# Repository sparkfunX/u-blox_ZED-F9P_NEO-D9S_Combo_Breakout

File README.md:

# SparkX u-blox ZED-F9P NEO-D9S Combo Breakout

<p align="center">

</p>

*[SparkX u-blox ZED-F9P NEO-D9S Combo Breakout (SPX-20167)](https://www.sparkfun.com/products/20167)*

The [SparkX u-blox ZED-F9P NEO-D9S Combo Breakout (SPX-20167)](https://www.sparkfun.com/products/20167) combines the u-blox ZED-F9P multi-band high precision GNSS module
with the NEO-D9S L-band GNSS correction data receiver. With a clear view of the sky, especially a clear view to the South, this combo breakout will deliver centimeter-level
accuracy positioning without needing separate RTK or NTRIP corrections.

The Combo Breakout is designed to work with u-blox's PointPerfect L-band satellite GNSS augmentation service, which provides homogeneous coverage in contiguous USA and Europe.

### Important Note:

u-blox provides products and services to "B2B Customers". Only business customers are eligible to register for a Thingstream (PointPerfect) account. You may be required to demonstrate that the use of the combo breakout is in relation to your trade, business, craft or profession. u-blox products and services are not intended for individual consumer use.

## Repository Contents

* **[/docs](/docs/)** - Online documentation files
    * [board_files](/docs/board_files/) - Files for the product design
        * [Eagle design files](/docs/board_files/ZED-F9P_NEO-D9S_Combo_x02.zip) (.zip)
        * [Schematic](/docs/board_files/Schematic.pdf) (.pdf)
        * [Dimensions](/docs/board_files/Dimensions.png) (.png)
    * [img/hookup_guide/](/docs/img/hookup_guide/) - Images for hookup guide documentation
* **[/Hardware](/Hardware/)** - Eagle design files (.brd, .sch)

## Documentation

* **[Hookup Guide (mkdocs)](https://sparkfunx.github.io/u-blox_ZED-F9P_NEO-D9S_Combo_Breakout)** - Hookup guide for the SparkX u-blox ZED-F9P NEO-D9S Combo Breakout hosted by GitHub pages.

## Product Versions

* [SPX-20167](https://www.sparkfun.com/products/20167) - Initial SparkX Release

## License Information

This product is _**open source**_! 

Please review the LICENSE.md file for license information. 

If you have any questions or concerns on licensing, please contact technical support on our [SparkFun forums](https://forum.sparkfun.com/viewforum.php?f=152).

Distributed as-is; no warranty is given.

- Your friends at SparkFun.

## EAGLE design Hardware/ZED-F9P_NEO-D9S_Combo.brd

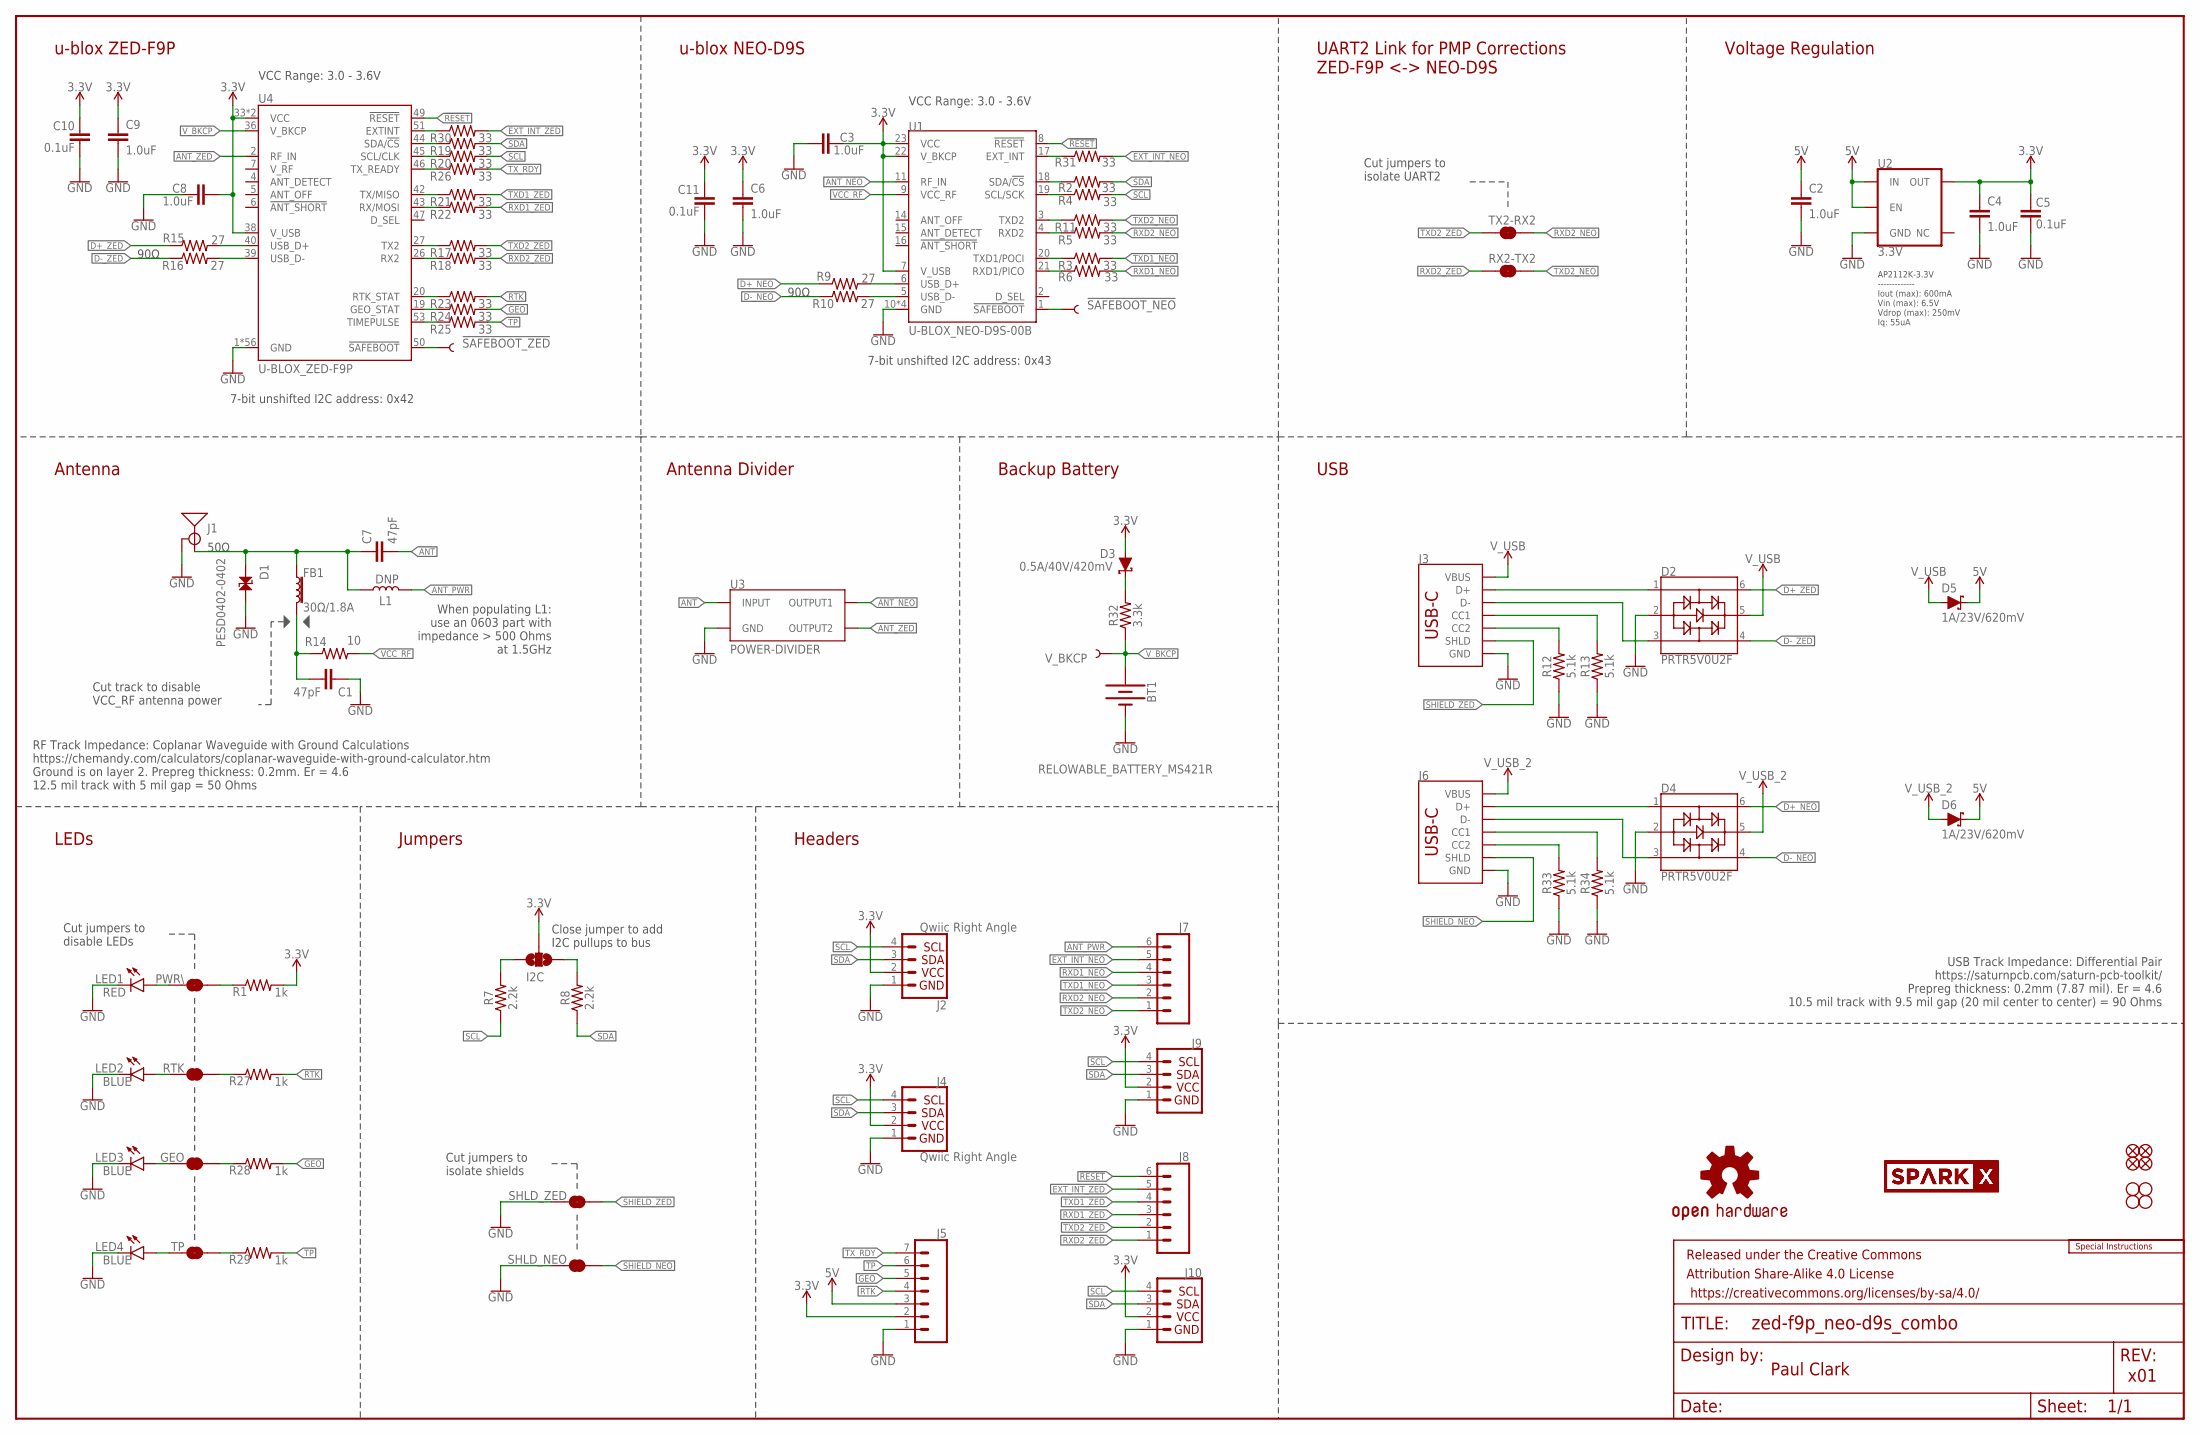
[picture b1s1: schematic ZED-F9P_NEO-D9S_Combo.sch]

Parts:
!SAFEBOOT_NEO!: TEST-POINTPOGO_PTH; 1X01_NO_SILK
!SAFEBOOT_ZED!: TEST-POINTPOGO_PTH; 1X01_NO_SILK
BT1: RELOWABLE_BATTERY_MS421R; MS421R_IV03E
C1, C7: 47pF; 0603
C2, C3, C4, C6, C8, C9: 1.0uF; 0603
C5, C10, C11: 0.1uF; 0603
D1: PESD0402-0402; 0402
D2, D4: PRTR5V0U2F; SOT886
D3: 0.5A/40V/420mV; SOD-323
D5, D6: 1A/23V/620mV; SOD-323
FB1: 30Ω/1.8A; 0603
FRAME2: FRAME-LEDGER; CREATIVE_COMMONS
GEO: JUMPER-SMT_2_NC_TRACE_SILK; SMT-JUMPER_2_NC_TRACE_SILK
I2C: JUMPER-SMT_3_NO_SILK; SMT-JUMPER_3_NO_SILK
J1: ANTENNA-SMA-GROUNDEDEDGE_SMA; SMA-EDGE
J2, J4: Qwiic Right Angle; JST04_1MM_RA
J3, J6: USB Female Type C Connector; USB-C-16P_4LAYER-PADS
J5: CONN_07NO_SILK; 1X07_NO_SILK
J7, J8: CONN_06NO_SILK_FEMALE_PTH; 1X06_NO_SILK
J9, J10: I2C_STANDARD_NO_SILK; 1X04_NO_SILK
JP21, JP61, JP71, JP81: FIDUCIALUFIDUCIAL; MICRO-FIDUCIAL
JP31, JP41, JP91, JP101: STAND-OFF
L1: DNP; 0603_NO-CREAM
LED1: RED; LED-0603
LED2, LED3, LED4: BLUE; LED-0603
LOGO4: OSHW-LOGOS; OSHW-LOGO-S
LOGO5: SPECIAL_INSTRUCTIONS-ORDERING; ORDERING_INSTRUCTIONS
PWR\: JUMPER-SMT_2_NC_TRACE_SILK; SMT-JUMPER_2_NC_TRACE_SILK
R1, R27, R28, R29: 1k; 0603
R2, R3, R4, R5, R6, R11, R17, R18, R19, R20, R21, R22, R23, R24, R25, R26, R30, R31: 33; 0603
R7, R8: 2.2k; 0603
R9, R10, R15, R16: 27; 0603
R12, R13, R33, R34: 5.1k; 0603
R14: 10; 0603
R32: 3.3k; 0603
RTK: JUMPER-SMT_2_NC_TRACE_SILK; SMT-JUMPER_2_NC_TRACE_SILK
RX2-TX2: JUMPER-SMT_2_NC_TRACE_SILK; SMT-JUMPER_2_NC_TRACE_SILK
SHLD_NEO: JUMPER-SMT_2_NC_TRACE_SILK; SMT-JUMPER_2_NC_TRACE_SILK
SHLD_ZED: JUMPER-SMT_2_NC_TRACE_SILK; SMT-JUMPER_2_NC_TRACE_SILK
TP: JUMPER-SMT_2_NC_TRACE_SILK; SMT-JUMPER_2_NC_TRACE_SILK
TX2-RX2: JUMPER-SMT_2_NC_TRACE_SILK; SMT-JUMPER_2_NC_TRACE_SILK
U1: U-BLOX_NEO-D9S-00B; NEO-M9N/M8T/M8U/D9S
U2: 3.3V; SOT23-5
U3: POWER-DIVIDER; PD0922J5050S2HF_ANA
U4: U-BLOX_ZED-F9P; ZED-F9P
U$77, U$78: SPARKX-LOGO4; SPARKX-MEDIUM
V_BKCP: TEST-POINT3X5; PAD.03X.05

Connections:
3.3V: C3.1, C4.1, C5.2, C6.1, C8.2, C9.1, C10.2, C11.2, D3.A, I2C.2, J2.2, J4.2, J5.2, J9.2, J10.2, R1.2, U1.7 (V_USB), U1.22 (V_BKCP), U1.23 (VCC), U2.5 (OUT), U4.33 (VCC), U4.34 (VCC), U4.38 (V_USB)
5V: C2.1, D5.C, D6.C, J5.3, U2.1 (IN), U2.3 (EN)
!RESET!: J8.6, U1.8 (!RESET!), U4.49 (!RESET!)
!SAFEBOOT_NEO!: !SAFEBOOT_NEO!.1, U1.1 (!SAFEBOOT!)
!SAFEBOOT_ZED!: !SAFEBOOT_ZED!.1, U4.50 (!SAFEBOOT!)
ANT: C7.2, U3.2 (INPUT)
ANT_NEO: U1.11 (RF_IN), U3.4 (OUTPUT1)
ANT_PWR: J7.6, L1.2
ANT_VCC: C1.1, FB1.2, R14.1
ANT_ZED: U3.6 (OUTPUT2), U4.2 (RF_IN)
D+_NEO: D4.6, R9.1
D+_ZED: D2.6, R15.1
D-_NEO: D4.4, R10.1
D-_ZED: D2.4, R16.1
EXT_INT_NEO: J7.5, R31.2
EXT_INT_ZED: J8.5, R30.2
GEO: J5.5, R24.2, R28.2
GND: BT1.-, C1.2, C2.2, C3.2, C4.2, C5.1, C6.2, C8.1, C9.2, C10.1, C11.1, D1.2, D2.2, D4.2, J1.GND@0 (GND), J1.GND@1 (GND), J1.GND@2 (GND), J1.GND@3 (GND), J2.1, J3.GND, J3.GND2 (GND), J4.1, J5.1, J6.GND, J6.GND2 (GND), J9.1, J10.1, LED1.C, LED2.C, LED3.C, LED4.C, R12.1, R13.1, R33.1, R34.1, SHLD_NEO.1, SHLD_ZED.1, U1.10 (GND), U1.12 (GND), U1.13 (GND), U1.24 (GND), U2.2 (GND), U3.1 (GND), U3.3 (GND), U3.5 (GND), U4.1 (GND), U4.3 (GND), U4.12 (GND), U4.14 (GND), U4.32 (GND), U4.37 (GND), U4.41 (GND), U4.48 (GND), U4.55 (GND), U4.56 (GND), U4.57 (GND), U4.58 (GND), U4.59 (GND), U4.60 (GND), U4.61 (GND), U4.62 (GND), U4.63 (GND), U4.64 (GND), U4.65 (GND), U4.66 (GND), U4.67 (GND), U4.68 (GND), U4.69 (GND), U4.70 (GND), U4.71 (GND), U4.72 (GND), U4.73 (GND), U4.74 (GND), U4.75 (GND), U4.76 (GND), U4.77 (GND), U4.78 (GND), U4.79 (GND), U4.80 (GND), U4.81 (GND), U4.82 (GND), U4.83 (GND), U4.84 (GND), U4.85 (GND), U4.86 (GND), U4.87 (GND), U4.88 (GND), U4.89 (GND), U4.90 (GND), U4.91 (GND), U4.92 (GND), U4.93 (GND), U4.94 (GND), U4.95 (GND), U4.96 (GND), U4.97 (GND), U4.98 (GND), U4.99 (GND), U4.100 (GND), U4.101 (GND), U4.102 (GND)
unnamed: PWR\.2, R1.1
unnamed: R3.1, U1.20 (TXD1/POCI)
unnamed: R2.1, U1.18 (SDA/!CS!)
unnamed: R4.1, U1.19 (SCL/SCK)
unnamed: I2C.1, R8.2
unnamed: R6.1, U1.21 (RXD1/PICO)
unnamed: J3.B5 (CC2), R12.2
unnamed: I2C.3, R7.2
unnamed: J3.A5 (CC1), R13.2
unnamed: LED1.A, PWR\.1
unnamed: R9.2, U1.6 (USB_D+)
unnamed: R10.2, U1.5 (USB_D-)
unnamed: D3.C, R32.2
unnamed: R11.1, U1.3 (TXD2)
unnamed: R5.1, U1.4 (RXD2)
unnamed: R15.2, U4.40 (USB_D+)
unnamed: R16.2, U4.39 (USB_D-)
unnamed: R19.1, U4.44 (SDA/!CS!)
unnamed: R20.1, U4.45 (SCL/CLK)
unnamed: R21.1, U4.42 (TX/MISO)
unnamed: R22.1, U4.43 (RX/MOSI)
unnamed: R26.1, U4.46 (TX_READY)
unnamed: LED2.A, RTK.1
unnamed: R17.1, U4.27 (TX2)
unnamed: R18.1, U4.26 (RX2)
unnamed: GEO.1, LED3.A
unnamed: LED4.A, TP.1
unnamed: R27.1, RTK.2
unnamed: GEO.2, R28.1
unnamed: R29.1, TP.2
unnamed: R30.1, U4.51 (EXTINT)
unnamed: R31.1, U1.17 (EXT_INT)
unnamed: J6.B5 (CC2), R33.2
unnamed: J6.A5 (CC1), R34.2
unnamed: R23.1, U4.20 (RTK_STAT)
unnamed: R24.1, U4.19 (GEO_STAT)
unnamed: R25.1, U4.53 (TIMEPULSE)
RTK: J5.4, R23.2, R27.2
RXD1_NEO: J7.4, R6.2
RXD1_ZED: J8.3, R22.2
RXD2_NEO: J7.2, R5.2, TX2-RX2.2
RXD2_ZED: J8.1, R18.2, RX2-TX2.1
SCL: J2.4, J4.4, J9.4, J10.4, R4.2, R7.1, R20.2
SDA: J2.3, J4.3, J9.3, J10.3, R2.2, R8.1, R19.2
SHIELD_NEO: J6.SHLD1 (SHLD), J6.SHLD2 (SHLD), J6.SHLD3 (SHLD), J6.SHLD4 (SHLD), SHLD_NEO.2
SHIELD_ZED: J3.SHLD1 (SHLD), J3.SHLD2 (SHLD), J3.SHLD3 (SHLD), J3.SHLD4 (SHLD), SHLD_ZED.2
SMA: C7.1, D1.1, FB1.1, J1.SIG (SIGNAL), L1.1
TP: J5.6, R25.2, R29.2
TXD1_NEO: J7.3, R3.2
TXD1_ZED: J8.4, R21.2
TXD2_NEO: J7.1, R11.2, RX2-TX2.2
TXD2_ZED: J8.2, R17.2, TX2-RX2.1
TX_RDY: J5.7, R26.2
USB_D+: D2.1, J3.A6 (D+), J3.B6 (D+)
USB_D+1: D4.1, J6.A6 (D+), J6.B6 (D+)
USB_D-: D2.3, J3.A7 (D-), J3.B7 (D-)
USB_D-1: D4.3, J6.A7 (D-), J6.B7 (D-)
VCC_RF: R14.2, U1.9 (VCC_RF)
V_BKCP: BT1.+, R32.1, U4.36 (V_BKCP), V_BKCP.1
V_USB: D2.5, D5.A, J3.VBUS1 (VBUS), J3.VBUS2 (VBUS)
V_USB_2: D4.5, D6.A, J6.VBUS1 (VBUS), J6.VBUS2 (VBUS)

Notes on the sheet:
x01
7-bit unshifted I2C address: 0x43
Close jumper to add I2C pullups to bus
Cut jumpers to disable LEDs
Paul Clark
Headers
LEDs
u-blox NEO-D9S
Antenna
USB
VCC Range: 3.0 - 3.6V
Cut jumpers to isolate shields
50Ω
Cut track to disable VCC_RF antenna power
90Ω
When populating L1: use an 0603 part with impedance > 500 Ohms at 1.5GHz
AP2112K-3.3V ------------- Iout (max): 600mA Vin (max): 6.5V Vdrop (max): 250mV Iq: 55uA
7-bit unshifted I2C address: 0x42
u-blox ZED-F9P
Antenna Divider
Jumpers
Backup Battery
Cut jumpers to isolate UART2
Voltage Regulation
RF Track Impedance: Coplanar Waveguide with Ground Calculations https://chemandy.com/calculators/coplanar-waveguide-with-ground-calculator.htm Ground is on layer 2. Prepreg thickness: 0.2mm. Er = 4.6 12.5 mil track with 5 mil gap = 50 Ohms
USB Track Impedance: Differential Pair https://saturnpcb.com/saturn-pcb-toolkit/ Prepreg thickness: 0.2mm (7.87 mil). Er = 4.6 10.5 mil track with 9.5 mil gap (20 mil center to center) = 90 Ohms
UART2 Link for PMP Corrections ZED-F9P <-> NEO-D9S

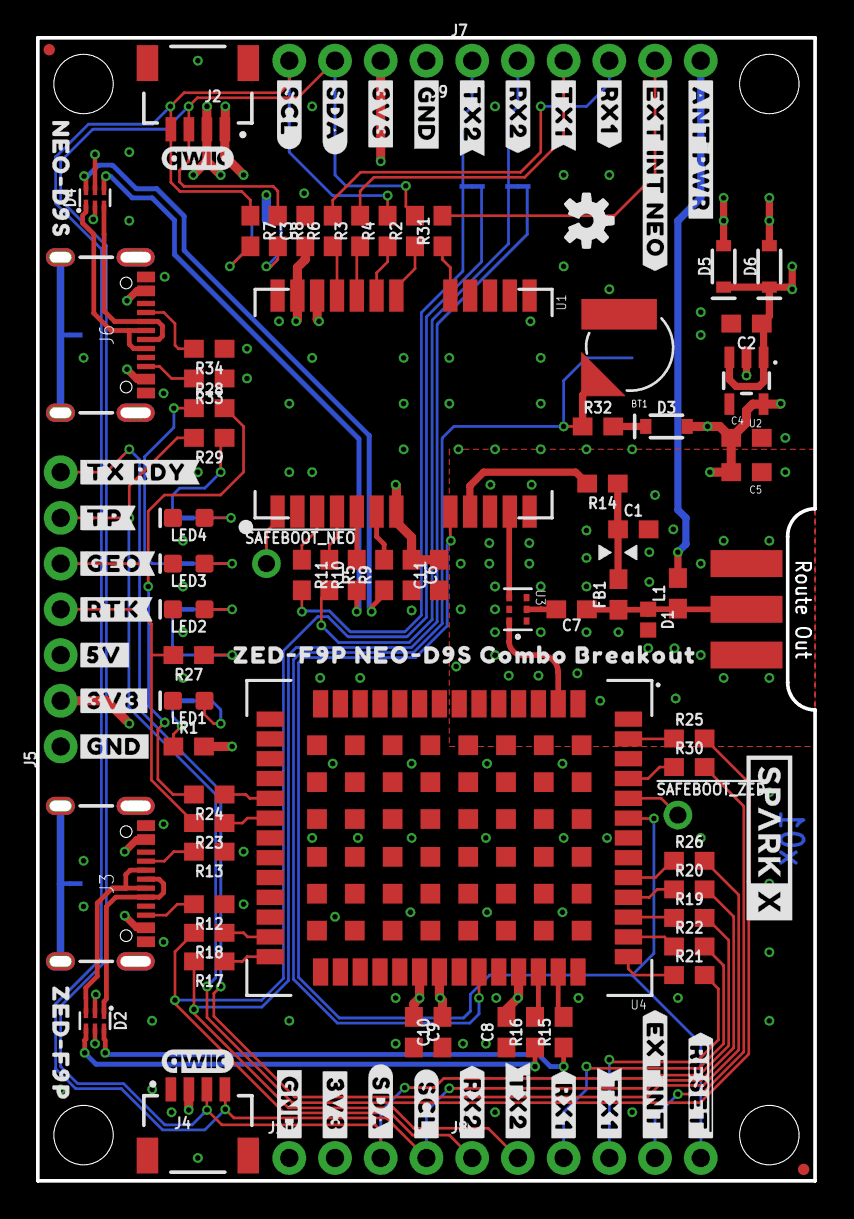
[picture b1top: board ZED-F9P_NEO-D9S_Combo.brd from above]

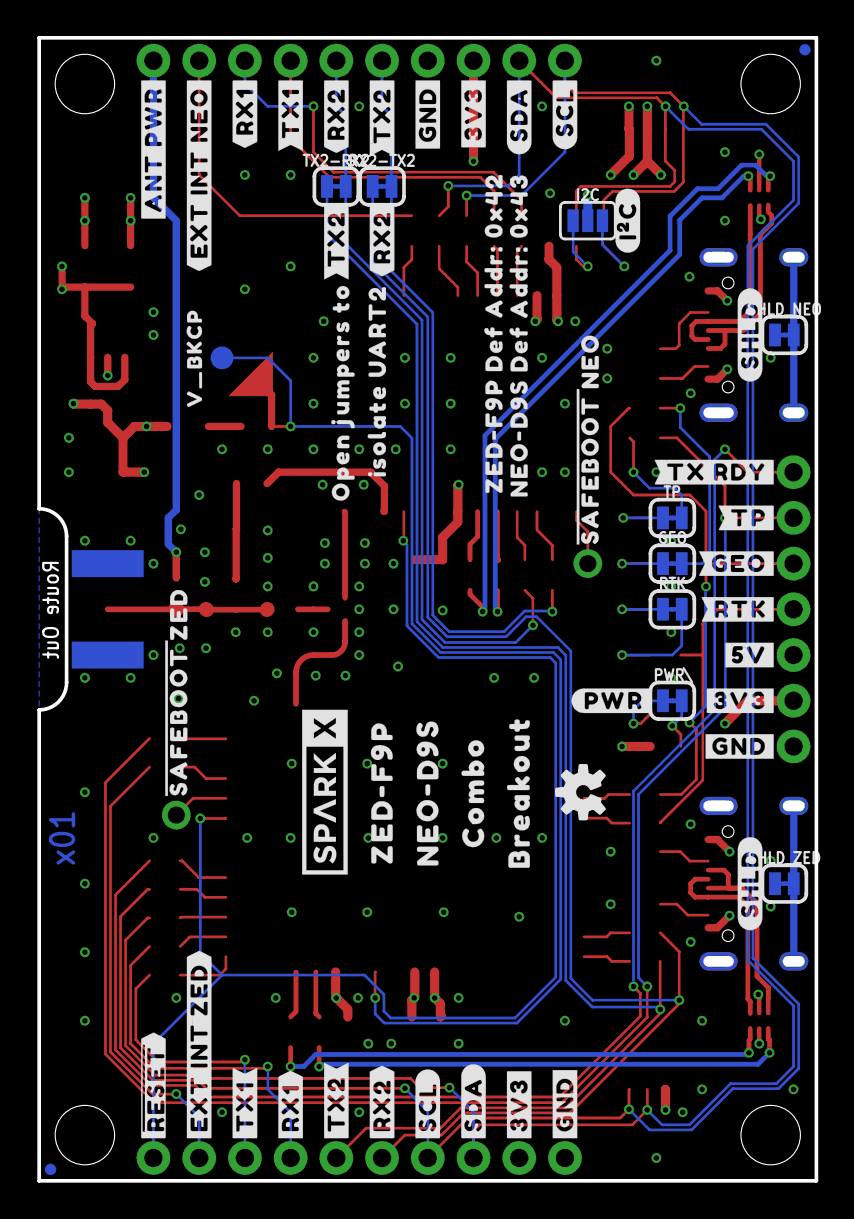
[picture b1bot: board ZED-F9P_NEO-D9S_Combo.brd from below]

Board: 4 copper layers, 43.2 x 63.5 mm, 174 parts (58 on the bottom side), 79 nets.

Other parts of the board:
LOGO1: OSHW-LOGOS; OSHW-LOGO-S
U$1, U$2, U$3: #GND#0
U$4, U$5, U$6: #GND#1
U$7, U$53: #SHLD#0
U$8, U$10: #SDA#0
U$9, U$13: #SCL#0
U$11, U$12: #SDA#1
U$14, U$38: QWIIC_4MM
U$15, U$30: #SCL#1
U$16: #RTK#0
U$17: #RTK#1
U$18: #GEO#0
U$19: #GEO#1
U$20: #5V#0
U$21: #5V#6
U$22, U$23, U$56: #3V3#0
U$24, U$25, U$70: #3V3#4
U$26: #TP#0
U$27: #TP#1
U$28: #TX_RDY#0
U$29: #TX_RDY#1
U$31, U$39, U$40: #TX2#0
U$32, U$34, U$35: #RX2#0
U$33: OPEN_JUMPERS_TO0
U$36, U$37: #RX2#3
U$41, U$42: #TX2#3
U$43, U$44: #RX1#0
U$45: ##RESET##0
U$46: ##RESET##1
U$47: #EXT_INT#0
U$48: #EXT_INT_ZED#0
U$49, U$50: #RX1#2
U$51, U$57: #TX1#0
U$52: #I�C#0
U$54: ISOLATE_UART21
U$55: NEO#D9S0
U$58: #ANT_PWR#0
U$59: #ANT_PWR#1
U$60, U$61: #TX1#2
U$62: #EXT_INT_NEO#0
U$63: #EXT_INT_NEO#1
U$64: ZED#F9P0
U$65: ZED#F9P10
U$66: NEO#D9S10
U$67: COMBO10
U$68: BREAKOUT11
U$69: #PWR#0
U$71: #SAFEBOOT#_NEO0
U$72: #SAFEBOOT#_ZED0
U$73: NEO#D9S_DEF_ADDR#_0X4310
U$74: ZED#F9P_DEF_ADDR#_0X420
U$75: ZED#F9P_NEO#D9S_COMBO_BREAKOUT0
U$76: V_BKCP0

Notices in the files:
README.md:
License: CC BY-SA 4.0
parts and their libraries:
SparkFun-Resistors: Licensing: Creative Commons ShareAlike 4.0 International - https://creativecommons.org/licenses/by-sa/4.0
SparkFun-Aesthetics: Released under the Creative Commons Attribution Share-Alike 4.0 License
SparkFun-Aesthetics: https://creativecommons.org/licenses/by-sa/4.0
